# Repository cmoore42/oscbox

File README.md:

# oscbox
Encoders for the ETC EOS family of lighting consoles using OSC and an Orange Pi Zero

## Overview
The purpose of this project is to create encoder wheels for the ETC EOS family of lighting software.
Specifically, the target is a PC or Mac running the EOS software.
It's possible this would work with a physical lighting console but it hasn't been tested.

The project was inspired by ETC's "lighthack" project.  
Their "box_1" implements two encoder wheels, one for PAN and one for TILT.
I wanted the same, but I wanted four wheels to match the wheels on an Ion console, 
and I wanted the wheels to be multi-function like the console wheels are.

## Details
For detailed descriptions of the code, the hardware, and the enclosure, [see the Wiki](https://github.com/cmoore42/oscbox/wiki)

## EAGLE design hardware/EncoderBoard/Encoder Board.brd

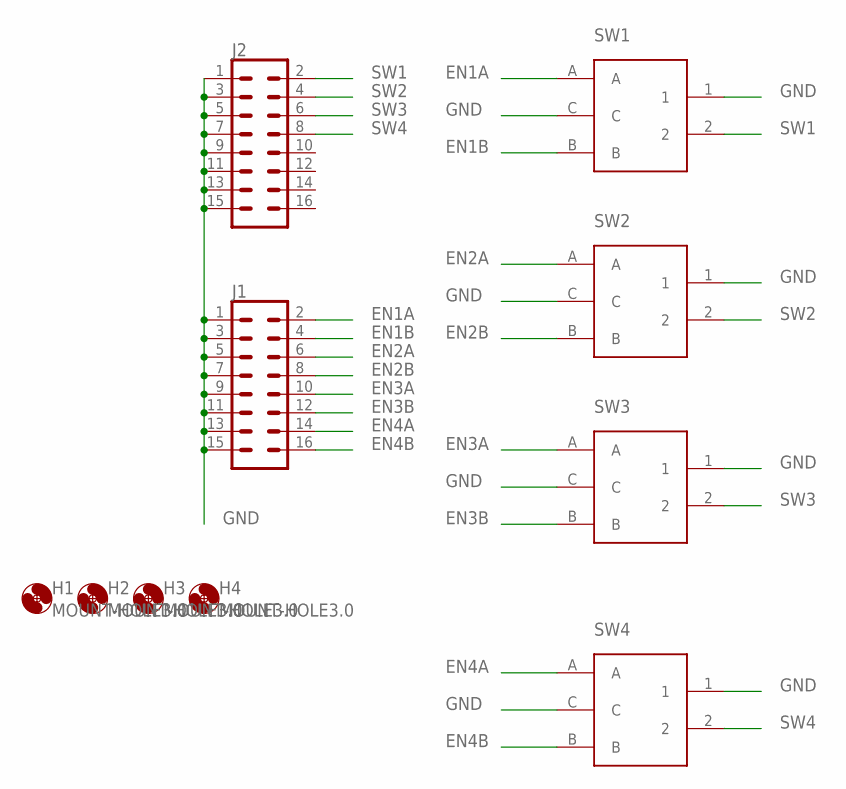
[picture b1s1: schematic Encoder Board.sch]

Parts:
H1, H2, H3, H4: MOUNT-HOLE3.0; 3,0
J1, J2: CONN_08X2; 2X8
SW1, SW2, SW3, SW4: PEC11R-4220F-S0012-ND; PEC11R-4XXXF-SXXXX

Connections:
EN1A: J1.2, SW1.A
EN1B: J1.4, SW1.B
EN2A: J1.6, SW2.A
EN2B: J1.8, SW2.B
EN3A: J1.10, SW3.A
EN3B: J1.12, SW3.B
EN4A: J1.14, SW4.A
EN4B: J1.16, SW4.B
GND: J1.1, J1.3, J1.5, J1.7, J1.9, J1.11, J1.13, J1.15, J2.1, J2.3, J2.5, J2.7, J2.9, J2.11, J2.13, J2.15, SW1.1, SW1.C, SW2.1, SW2.C, SW3.1, SW3.C, SW4.1, SW4.C
SW1: J2.2, SW1.2
SW2: J2.4, SW2.2
SW3: J2.6, SW3.2
SW4: J2.8, SW4.2

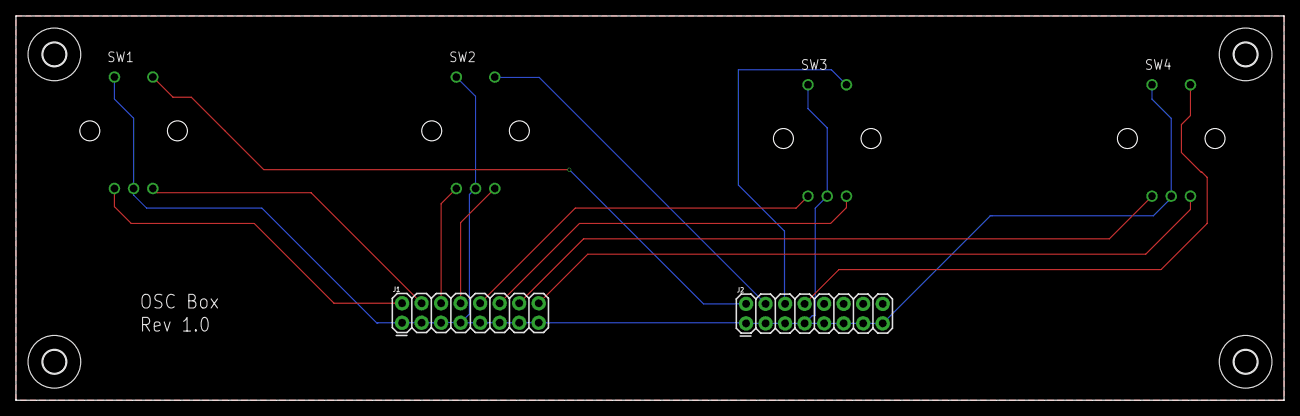
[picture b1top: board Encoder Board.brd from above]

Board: 2 copper layers, 165.0 x 50.0 mm, 10 parts (0 on the bottom side), 13 nets.

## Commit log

2019-07-24 Initial check in
2019-07-24 Added tinyosc.h
2019-07-27 Added I2C functions. Files i2c.c and i2c.h for communicating with the I2C based I/O expander. GPIO function modified to watch GPIO6 for an interrupt, then read the encoder values using I2C.
2019-07-29 Implemented interrupt processing from the I2C expander. The I2C expander now sends an interrupt when a GPIO pin changes. The main code sees the interrupt on GPIO line 6, reads the state of GPIO port 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
2019-07-30 Added tracking of wheel catagories Added a debug option Increased the number of wheels Fixed a bug in name_to_param
2019-08-05 Added code for writing to the frame buffer Also added a variety of test programs used during development
2019-08-06 Minor changes Added disp_clear_range() function Changed font to Tamzen8x15 Added touchscreen function to main - not yet implemented. Added some functions to the test directory Calculated mapping from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
2019-08-06 Restructuring of source files. Split a lot of code out of main.c into other files for better organization.
2019-08-06 Added code for processing touchscreen input. Cleaned up includes in main.c Added functions in main.c for creating buttons.
2019-08-06 Added category select buttons. Soft buttons on the touchscreen for focus, color, image, form, and shutter. Encoder names are displayed based on current category.
2019-08-06 Names for encoders are split over multiple lines
2019-08-06 Update encoder labels when values change
2019-08-08 Added encoder->wheel mapping in eos.c
2019-08-09 Added softkey buttons Parameterized the layout on the screen Added a SIGUSR1 handler, to dump the I2C registers Move the interrupt clear to just before the event wait
2019-08-11 Made the buttons and display boxes white on blue.
2019-09-10 Added a few files to .gitignore
2019-09-10 Restructuring the repo
    Moved all code into a "code" directory, created directories for hardware
    and enclosure designs.
2019-09-10 Added PC board design.
2019-09-10 Added SCAD and STL files for the 3D printed panel.

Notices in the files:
parts and their libraries:
SparkFun-Connectors: Licensing: Creative Commons ShareAlike 4.0 International - https://creativecommons.org/licenses/by-sa/4.0
